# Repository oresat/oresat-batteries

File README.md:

# OreSat Battery Card

This is the battery card for the OreSat system. You can have up to four of these cards in any OreSat system, ID is set by resistors.

## Version History

- v1.0: We don't talk about v1 (EAGLE).
- v2.0: First true pack with 3D printed cell storage. Many small issues (EAGLE).
- v3.0: Flight ready pack, flown 2021-03-15 on OreSat0. Worked! (EAGLE).
- v3.1: Imported into KiCAD, small tweaks in process (KiCAD).

## Bill of Materials

- [PCBA](https://docs.google.com/spreadsheets/d/11vG1kWyrAjmbF5QJM-EhXmvQoF6O47japwYlHF802do/edit#gid=576852939)
- [Assembly](https://docs.google.com/spreadsheets/d/1GmZE2MR5q2XFSR2Y-65dwwPd7tem3i0CEjZBlCLeJBU/edit?usp=sharing)

## Mechanical CAD

- In [OnShape](https://cad.onshape.com/documents/5eda02ab87dc9021603c3619/w/adac4deb8bbe537007a3b153/e/e3b4fa777f54f6382aedf8d8).

## Technical Information

- 2 independent 2S1P 18650 battery packs (4 batteries total, in 2 packs). Each pack has:
   - Battery protection circuitry for charge and discharge control for each 2S1P pack
   - MAX17500 fuel gauge with cell balancing and cell temperature monitoring
- 3D printed battery holder, designed for CRP Windform SLS Nylon material (OK with Form3 Flame Retardant Resin).
- Positive battery lead disconnection switches (with room for plunger assemblies that go through OreSat +/-X rails).
- Satellite shutdown switches (!SHUTDOWN) (with room for plunger assemblies that go through OreSat +/-X rails).
- Flexible polyimide heater tapes to keep batteries above 0 C
- STM32F091 microcontroller (controlled by the OreSat Power Domain) to interface everything to the CAN bus

## TRANSITION DOCUMENT
Documentation is moving to [Google Docs](https://docs.google.com/document/d/1yaPGtJSM5RQG5k7sVpsDxBkVu4CHtm4LMNnisgOaNRg/edit#heading=h.gjdgxs). The rest of this readme will be integrated later.

## OreSat Vbus
OreSat main power bus is just our 2S Li Ion battery pack, which we've defined as 6.0 V minimum, 7.2 V typical, and 8.4 V maximum. Everything is directly connected to that bus, including:

- Other Oreat battery cards. For >= 2U CubeSats, you'll probably have at least two battery cards.
- All solar panels. Thus the solar panels see the direct battery voltage and can dump directly into the battery packs, thus doing _actual_ MPPT.
- All loads.

## Battery Card Topology
Confusingly, Each OreSat battery card has 2 independent battery packs on it. Each pack is made of a 2S1P 18650 LiPo cell pack. So it's a 2x2S1P if you will. Despite this, each card is independent and the OPD is fully capable of functioning with only one active card.

We decided to separate the packs instead of combining them into a single 2S2P pack for the sake of redundancy, we can lose one cell and the other pack can still provide power to the OPD, as opposed to losing an entire card from a single cell failure.  This design does come with the added drawbacks of extra overhead in the form of requiring more charge protection and fuel gauge circuitry.

## Charge/Discharge Protection
We are using Ablic S8209 to monitor our cell voltage levels and disable charging if the cell voltage goes above the predetermined overcharging threshold or disable discharging if the cell voltage goes below a predetermined discharging threshold.

The S8209 has two inputs that, if activated, will trigger the either the over-charge or under-charge protection to activate.  This allows us to daisy chain these chips together, so that each cell has its own charge protection IC.  It also allows us to connect them to a GPIO on an onboard microcontroller so that we can manually disable charging or discharging functionality if needed.  Below is a state diagram that depicts the desired behavior of our charging and discharging protection circuit

The output of the S8209 uses an internal N-channel MOSFET, which has the potential to latch from radiation exposure.   To combat this, we have P-channel MOSFETS in series with the VDD of each S8209, the gate of the MOSFET is connected to our onboard microcontroller, so that we can periodically power cycle the S8209 and clear the N-channel latch.

The actual control of charge and discharge are done using Linear LTC4412 ideal diode controllers. Totally bizarre, but indepdenently controllable!

## Fuel Gauge and Cell Health Monitoring
Each 2S1P battery back will have two MAX17205 fuel gauges to monitor the packs current state of charge, and the long term health of the battery.  Each MAX17205 will be reporting both the direct State of charge (in mAh) and the percentage over I2C to our M0, compensating for factors such as cell degradation and temperature ranges.  We are still testing the accuracy of the MAX17205's compensation algorithm's for extreme charge levels and temperature in our lab.  At this point we don't know how much we should be relying on these compensation algorithms, they could be amazing! Or horrible! We don't know! Yay science!

Each fuel gauge is also monitoring the battery temperatures with a single internal sensor and two external thermistors (we are still determining the best position for these thermistors).  This gives us a wackton of data which is good because we are data hoarders.

Finally the MAX17205 also does cell balancing, which we'll enable while charging.

## Heaters
Thermal models of both 1U and 2U CubeSats show an average "passive" battery temperature of ~ -10 C). That's not good. We can't charge the battery below 0 C. So we've added heaters to heat up the batteries when charging if necessary.

We're using two Minco HK6903 heaters in parallel. They have "vacuum OK" (apparently?) urethane PSA that we'll use to attach them to the batteries. Note that they're 12.7 x 100 mm, and each heater goes across both batteries. At 49 ohms +/- 10% each, that's 25 ohms in parallel. Unclear on the heater's tempco. We'll ignore for now.

- At 8.4V, that's 336 mA = 2.8 W (at 100% DC)
- At 6.0V, that's 240 mA = 1.4 W (at 100% DC)
- We can of course PWM them and reduce the power as necessary

With that much current draw, we're going to need to modify the OPD circuit breaker to allow more current.

## Batteries

- Tenergy model "30005-0 (ICR 18650-2600, LR1865SK)"
- Rated at 2600 mAh
- Max voltage: 4.2 V
- Typical voltage: 3.6 V
- Minimum voltage: 2.75 V
- Maximum charge current: 1.25 A
   - 0 - 45 C only
- Maximum discharge Current:
   - -20 - 5 C = 1.25 A
   -  5 - 45 C = 5 A
   - 45 - 60 C = 3.75 A

### Temperature

Just to summarize the battery temperature operational range:

- Cell temperature < -20 C -- DEAD
- Cell temperature < 0 C -- DISCHARGE ONLY
- Cell temperature < 45 C -- NORMAL OPERATION
- Cell temperature > 45 C-- DISCHARGE ONLY
- Cell temperature > 60 C-- DEAD

### Cell failure (short)

- Short will plummet battery to < 2.5V (Vlvco) and S-8209 will disconnect the battery from discharging but not charging

## Battery pack behaviors (circuitry + firmware)

- Automatic discharge if > 6.0 V
- Automatic slow charge if < 8.4 V
- Fast charge if battery pack within ~ 0.5 V of other batteries

## Hacking the OPD Circuit Breaker

The OPD circuit breaker is supposed to trip at 300 mA without any division at the current output. Since the headers could pull up to 336, we need to probably go up to that plus 50 mA. So we put in a 10K and 20K to make a 0.66 divider and an N CH MOSFET to turn on the divider on the signal "MOARPWR". Asserting MOARPWR should give you up to 400 mA.

## LICENSE

Copyright Portland State Aerospace Society 2020.

This documentation describes Open Hardware and is licensed under the CERN OHL v. 1.2.

You may redistribute and modify this documentation under the terms of the CERN OHL v.1.2. [http://ohwr.org/cernohl](http://ohwr.org/cernohl). This documentation is distributed WITHOUT ANY EXPRESS OR IMPLIED WARRANTY, INCLUDING OF MERCHANTABILITY, SATISFACTORY QUALITY AND FITNESS FOR A PARTICULAR PURPOSE. Please see the CERN OHL v.1.2 for applicable conditions.

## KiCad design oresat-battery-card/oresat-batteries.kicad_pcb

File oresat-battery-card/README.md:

---
title: "**OreSat Battery Card**"
subtitle: |
  **Fabrication and Assembly Information**\
  For build TIME-STAMP
fontsize: 10pt
geometry:
  - margin=0.5in
toc: true
toc-depth: 2
colorlinks: true
urlcolor: blue
---

\newpage

# About this Board

## Board Description

The OreSat Battery Card carries two packs of 2S1P 18650 Lithium Ion cells. It operates completely autonomously. The C3 card
can, however, turn on the Battery Card's OPD, which will enable the onboard microcontroller and the battery card will begin
sending telemetry over CAN, including from a fuel gauge for each battery pack.

The battery card has two heater strips, which firmware uses to heat the batteries to >= 5 C.

Their are four inhibit switches as well - two for the OreSat !SHUTDOWN circuit, one for positive battery disconnect, and 
one for negative battery disconnect.

## Documentation Links

- Git repository: <https://github.com/oresat/oresat-batteries>
- [Design Notes](https://docs.google.com/document/d/1yaPGtJSM5RQG5k7sVpsDxBkVu4CHtm4LMNnisgOaNRg/edit?usp=sharing)

## Documentation Files

| Filename                        | Notes                                    |
| ------------------------------- | ---------------------------------------- |
| README.pdf                      | This README file                         |
| PROJECT-NAME-outline.dxf        | Board outline (with holes) in DXF format |
| PROJECT-NAME-pcba.step          | 3D model of PCBA (with components)       |
| PROJECT-NAME-render-bot.jpg     | Render of the top of the 3D model        |
| PROJECT-NAME-render-bot.jpg     | Render of the bottom of the 3D model     |
| PROJECT-NAME-schematic.pdf      | PDF of board schematics                  |

## Contact Information

- Website: <https://www.oresat.org/>
- Email: <oresat@pdx.edu>
- Instagram: @pdxaerospace

## Board Renders

{width=50%}
{width=50%}

\newpage

# Printed Circuit Board (PCB) Fabrication Information

## Board Info

- 4 layer board
- Bounding box is 99.8 x 94.6 mm
- Board thickness is 1.59 mm

## Board Requirements

- Design Rules
    - Minimum Trace / Space design rules
       - Outer layers: 0.127 mm (5.0 mil) / 0.127 mm (5.0 mil)
       - Inner layers: 0.127 mm (5.0 mil) / 0.127 mm (5.0 mil)
    - Outer dimension router tolerance: +/- 0.254 mm (10.0 mil)
    - Hole placement tolerance: +/- 0.075 mm (3.0 mil)
    - Inner tab routed slot tolerance: +/- 0.254 mm (10.0 mil)
- Drills
   - Drill Positional Tolerance: 0.051 mm (2.0 mil)
   - Drill Size tolerance: +/- 0.064 mm (2.5 mil)
- Plated/Un-plated holes
  - Via/PTH minimum diameter: 0.254 mm (10 mil)
  - Via/PTH minimum annulus: 0.102 mm (4 mil) radius
- Outline/Routing
  - This board requires a 1 mm router bit.
- Slots
  - There are 16 slots.
- Cutouts
  - There are no cutouts
- There are 3 fiducials on the top layer.
- Panel tabs ("mouse bites")
   - Card edges must be smooth; no mouse bites or other intrusions into the card outline.
   - If external mouse bites are required, minimize and customer will remove by hand before assembly.
- If not otherwise specified, fabricate PCB to IPC 6012 Class 2 or better.

## Stackup /  Materials

- Outside copper layers is 1 oz Cu after plating (0.043 mm / 1.7 mil)
- Inside copper layers are 0.5 oz Cu (0.018 mm / 0.7 mil)
- There are no requirements on the prepreg or core of this four layer stackup.
- Board Surface treatment should be ENIG, althogh immersion Silver is acceptable.
- White silkscreen on top and bottom surface
- Taiyo PSR-4000 or equivalent soldermask on top and bottom, no requirements for color.

## Array / Panel Information

- Coordinate with Contract Manufacturer (CM) for optimal size of this panel.
- If no feedback from CM, then produce single boards (no panel).

## Fabrication Files

### IPC-2581 File

| Filename                 | Notes                                   |
| ------------------------ | --------------------------------------- |
| PROJECT-NAME-ipc2581.xml | IPC-2581 board information file         |

### Legacy PCB Files

| Filename                      | Notes                                         |
| ------------------------------| --------------------------------------------- |
| PROJECT-NAME-Edge_Cuts.gbr    | RS274X file for the dimension (outline) layer |
| PROJECT-NAME-F_Silkscreen.gbr | RS274X file for the top silkscreen            |
| PROJECT-NAME-F_Mask.gbr       | RS274X file for the top soldermask            |
| PROJECT-NAME-F_Cu.gbr         | RS274X file for the top copper layer          |
| PROJECT-NAME-In1_Cu.gbr       | RS274X file for the layer 2 copper            |
| PROJECT-NAME-In2_Cu.gbr       | RS274X file for the layer 3 copper            |
| PROJECT-NAME-B_Cu.gbr         | RS274X file for the bottom copper layer       |
| PROJECT-NAME-B_Mask.gbr       | RS274X file for the bottom soldermask         |
| PROJECT-NAME-B_Silkscreen.gbr | RS274X file for the bottom silkscreen         |
| PROJECT-NAME-NPTH.drl         | Excellon file for non-plated through holes    |
| PROJECT-NAME-PTH.drl          | Excellon file for plated through holes        | 

\newpage

# Printed Circuit Board Assembly (PCBA) Information

## Assembly Info

- All components are on the top side of the board.
- This PCBA uses both surface mount (SMT) and through-hole (THT) components.

## Assembly Requirements

- Assemble to IPC Class 2 or better
- Bake components that are not moisture sealed to appropriate levels as required.
- Any solder paste (leaded or RoHS) is acceptable. RoHS solder is slightly preferred.
- Any no-clean or aqueous wash flux is acceptable.
- No conformal coating.

## Component Specific Assembly Information

- ASSEMBLY OF THIS BATTERY CARD IS SAFETY CRITICAL. CAREFULLY FOLLOW THE ASSEMBLY SOP,
[PSAS SOP - OreSat Battery Card Assembly](https://docs.google.com/document/d/1YFvptCjQO5j7sZraa8bQpTQ43OzNet4JrRba6-A-SFA/edit?usp=sharing).

## Assembly Files

### IPC-2581 File

| Filename                 | Notes                           |
| ------------------------ | ------------------------------- |
| PROJECT-NAME-ipc2581.xml | IPC-2581 board information file |

### Bill of Materials (BOM)

| Filename             | Description                            |
| -------------------- | -------------------------------------- |
| PROJECT-NAME-bom.csv | BOM in Comma Separated Variable format |

### Solder Paste Stencils

| Filename                 | Notes                                            |
| ------------------------ | ------------------------------------------------ |
| PROJECT-NAME-B_Paste.gbr | RS274X file for top/front solder paste stencil   |
| PROJECT-NAME-F_Paste.gbr | RS274X file for bottom/back solder paste stencil |

### Mounting/Placement Location

| Filename            | Description                                 |
| ------------------- | ------------------------------------------- |
| PROJECT-NAME.pos | Pick and place locations for components     |

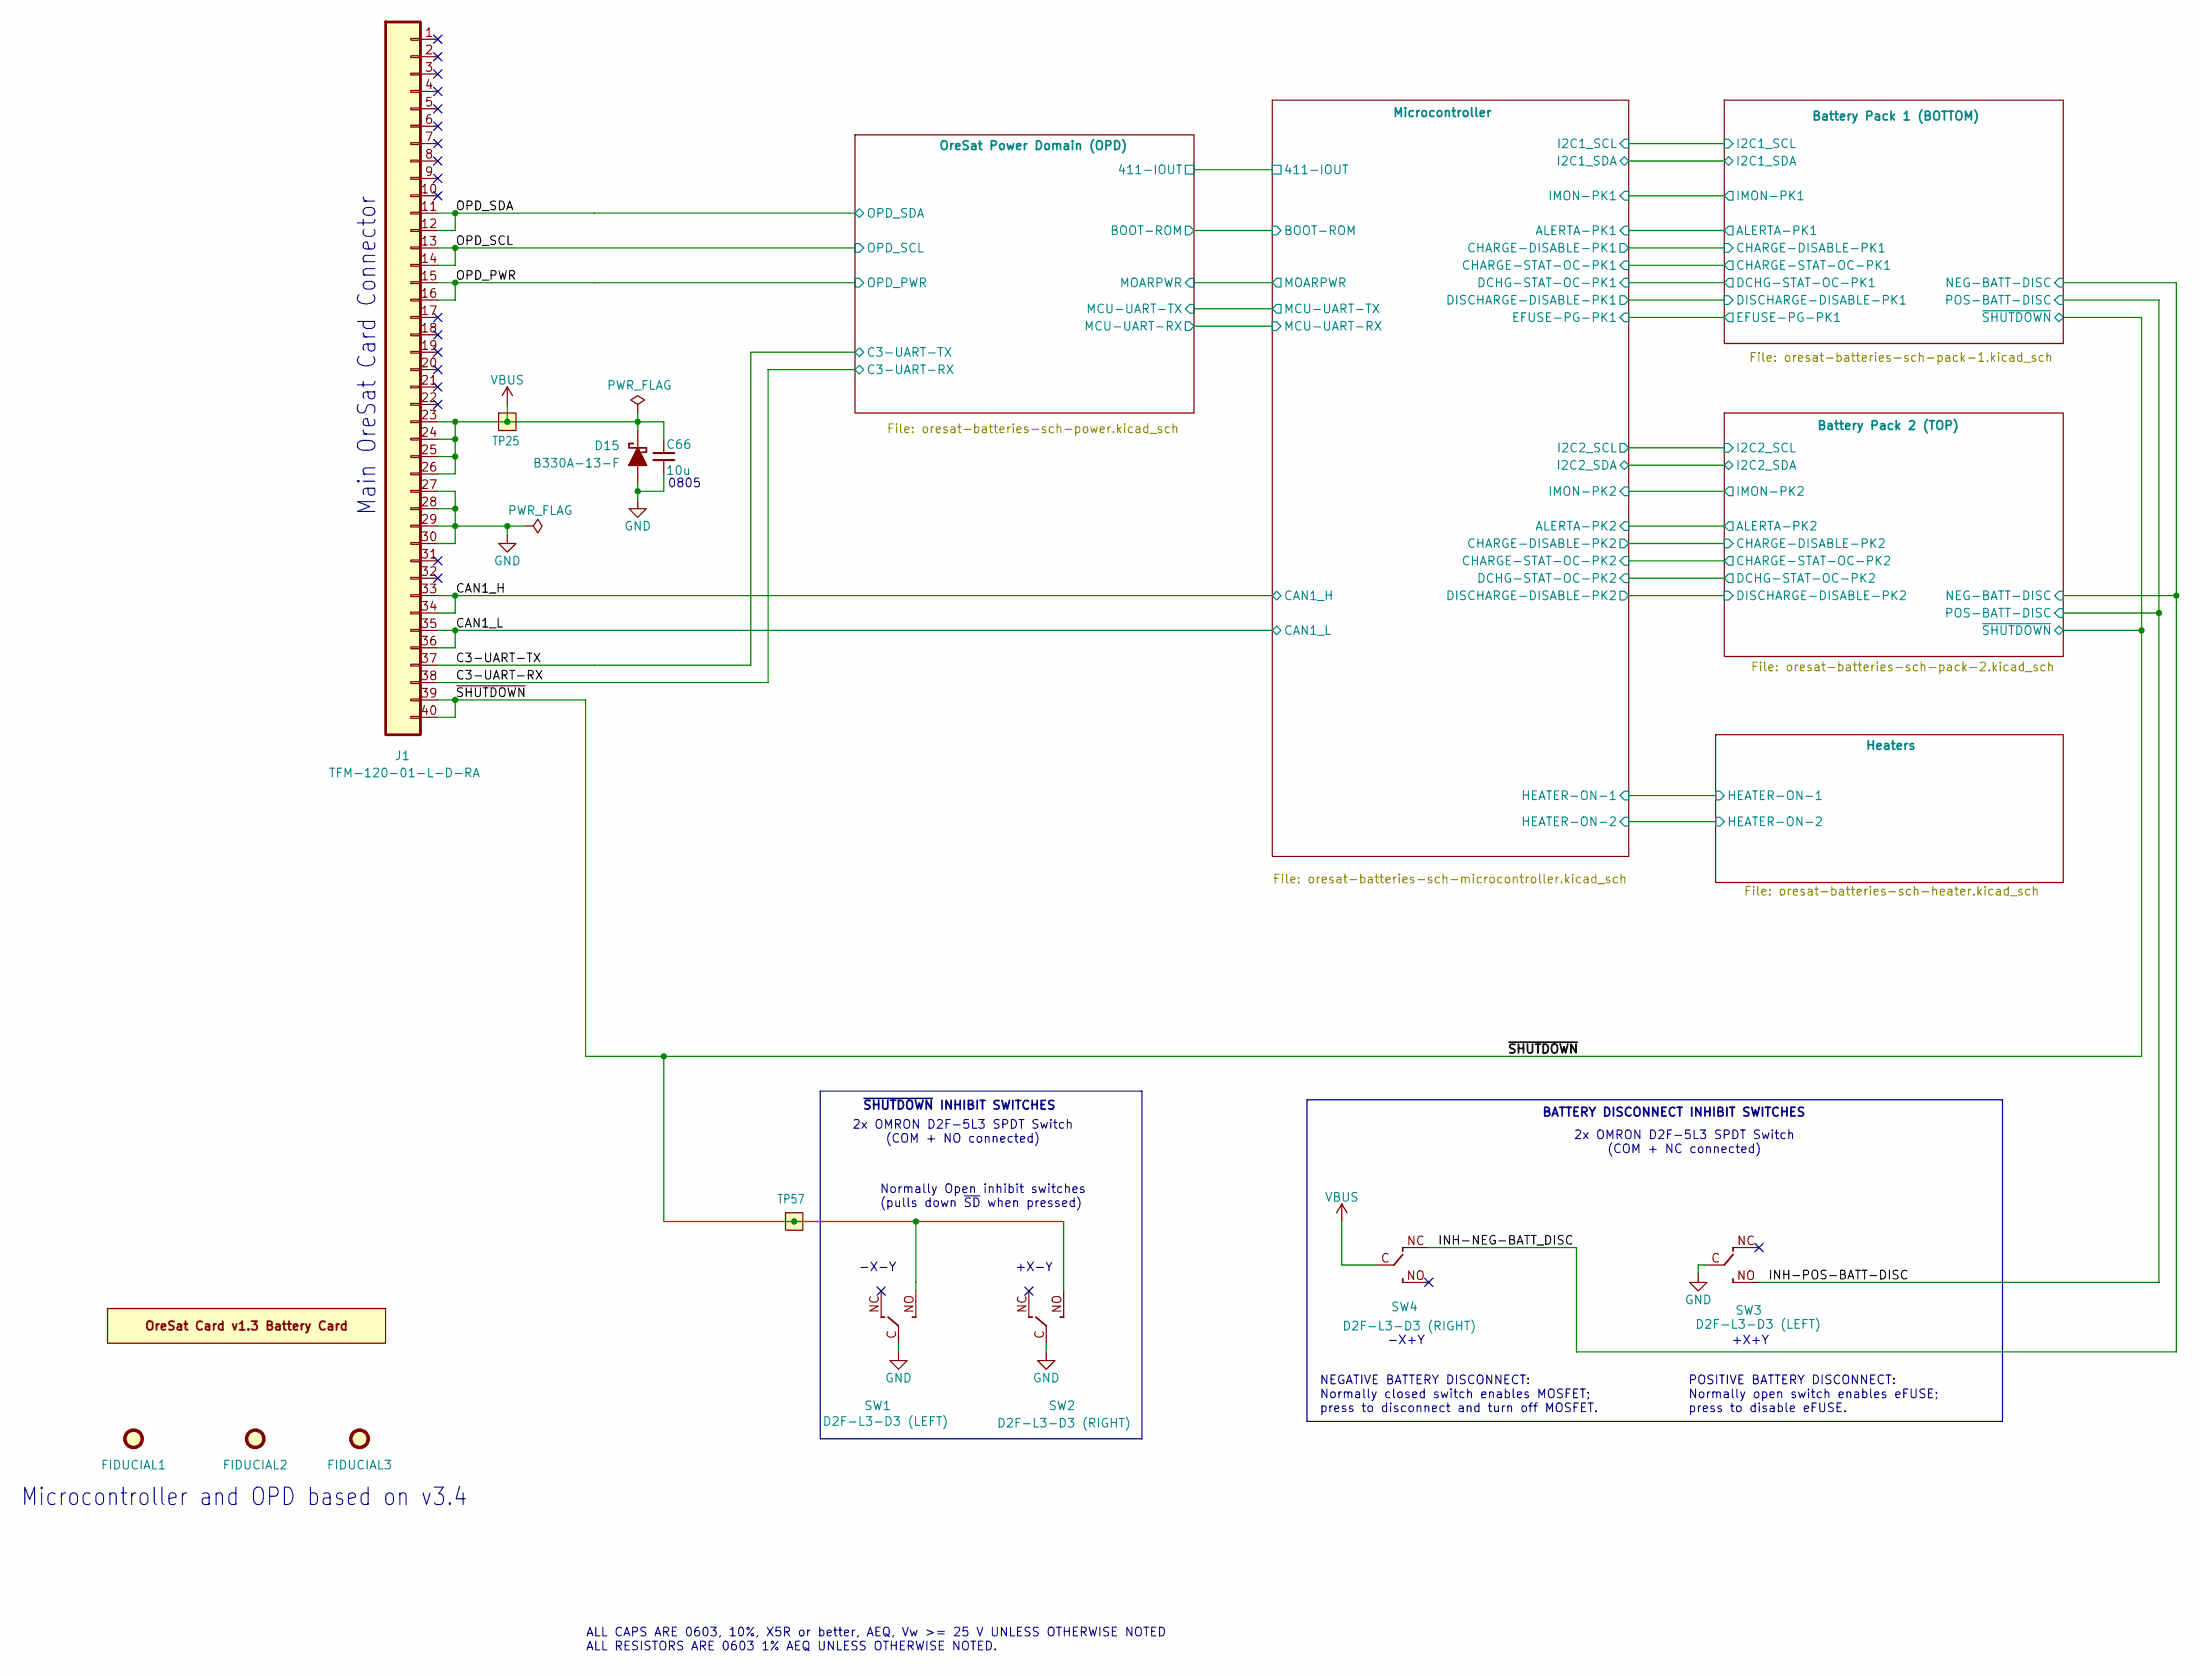
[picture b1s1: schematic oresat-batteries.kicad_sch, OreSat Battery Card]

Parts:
C66: 10u; 0805-C-NOSILK; MPN GRT21BC71E106KE13K
D15: B330A-13-F; D_SMA; MPN B330A-13-F
FIDUCIAL1, FIDUCIAL2, FIDUCIAL3: FIDUCIAL-1.0X2.0; Fiducial_1mm_Mask2mm
J1: TFM-120-01-L-D-RA; J-SAMTEC-TFM-120-X1-XXX-D-RA; MPN TFM-120-01-L-D-RA
PCB1: ORESAT-CARD-V1.3-BATTERY; ORESAT-CARD-V1.3-BATTERY-V3.0; MPN N/A
SW1, SW3: D2F-L3-D3 (LEFT); D2F-L3-D3-HORIZONTAL-L; MPN D2F-L3-D3
SW2, SW4: D2F-L3-D3 (RIGHT); D2F-L3-D3-HORIZONTAL-R; MPN D2F-L3-D3
TP25, TP57: TEST-POINT-LARGE-SQUARE; TestPoint-0.75mm-th

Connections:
/C3-UART-RX: J1.38; also elsewhere on the board
/C3-UART-TX: J1.37; also elsewhere on the board
/CAN1_H: J1.33, J1.34; also elsewhere on the board
/CAN1_L: J1.35, J1.36; also elsewhere on the board
/INH-NEG-BATT_DISC: SW4.NC; also elsewhere on the board
/INH-POS-BATT-DISC: SW3.NO; also elsewhere on the board
/OPD_PWR: J1.15, J1.16; also elsewhere on the board
/OPD_SCL: J1.13, J1.14; also elsewhere on the board
/OPD_SDA: J1.11, J1.12; also elsewhere on the board
/~SHUTDOWN: J1.39, J1.40, SW1.NO, SW2.NO, TP57.1 (1_1); also elsewhere on the board
GND: C66.2, D15.2 (A), J1.27, J1.28, J1.29, J1.30, SW1.C (COM), SW2.C (COM), SW3.C (COM); also elsewhere on the board
VBUS: C66.1, D15.1 (K), J1.23, J1.24, J1.25, J1.26, SW4.C (COM), TP25.1 (1_1); also elsewhere on the board

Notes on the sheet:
Normally Open inhibit switches (pulls down ~{SD} when pressed)
Main OreSat Card Connector
~{SHUTDOWN} INHIBIT SWITCHES
BATTERY DISCONNECT INHIBIT SWITCHES
+X+Y
2x OMRON D2F-5L3 SPDT Switch (COM + NO connected)
-X-Y
ALL CAPS ARE 0603, 10%, X5R or better, AEQ, Vw >= 25 V UNLESS OTHERWISE NOTED ALL RESISTORS ARE 0603 1% AEQ UNLESS OTHERWISE NOTED.
+X-Y
-X+Y
0805
Microcontroller and OPD based on v3.4
NEGATIVE BATTERY DISCONNECT: Normally closed switch enables MOSFET; press to disconnect and turn off MOSFET.
2x OMRON D2F-5L3 SPDT Switch (COM + NC connected)
POSITIVE BATTERY DISCONNECT: Normally open switch enables eFUSE; press to disable eFUSE.

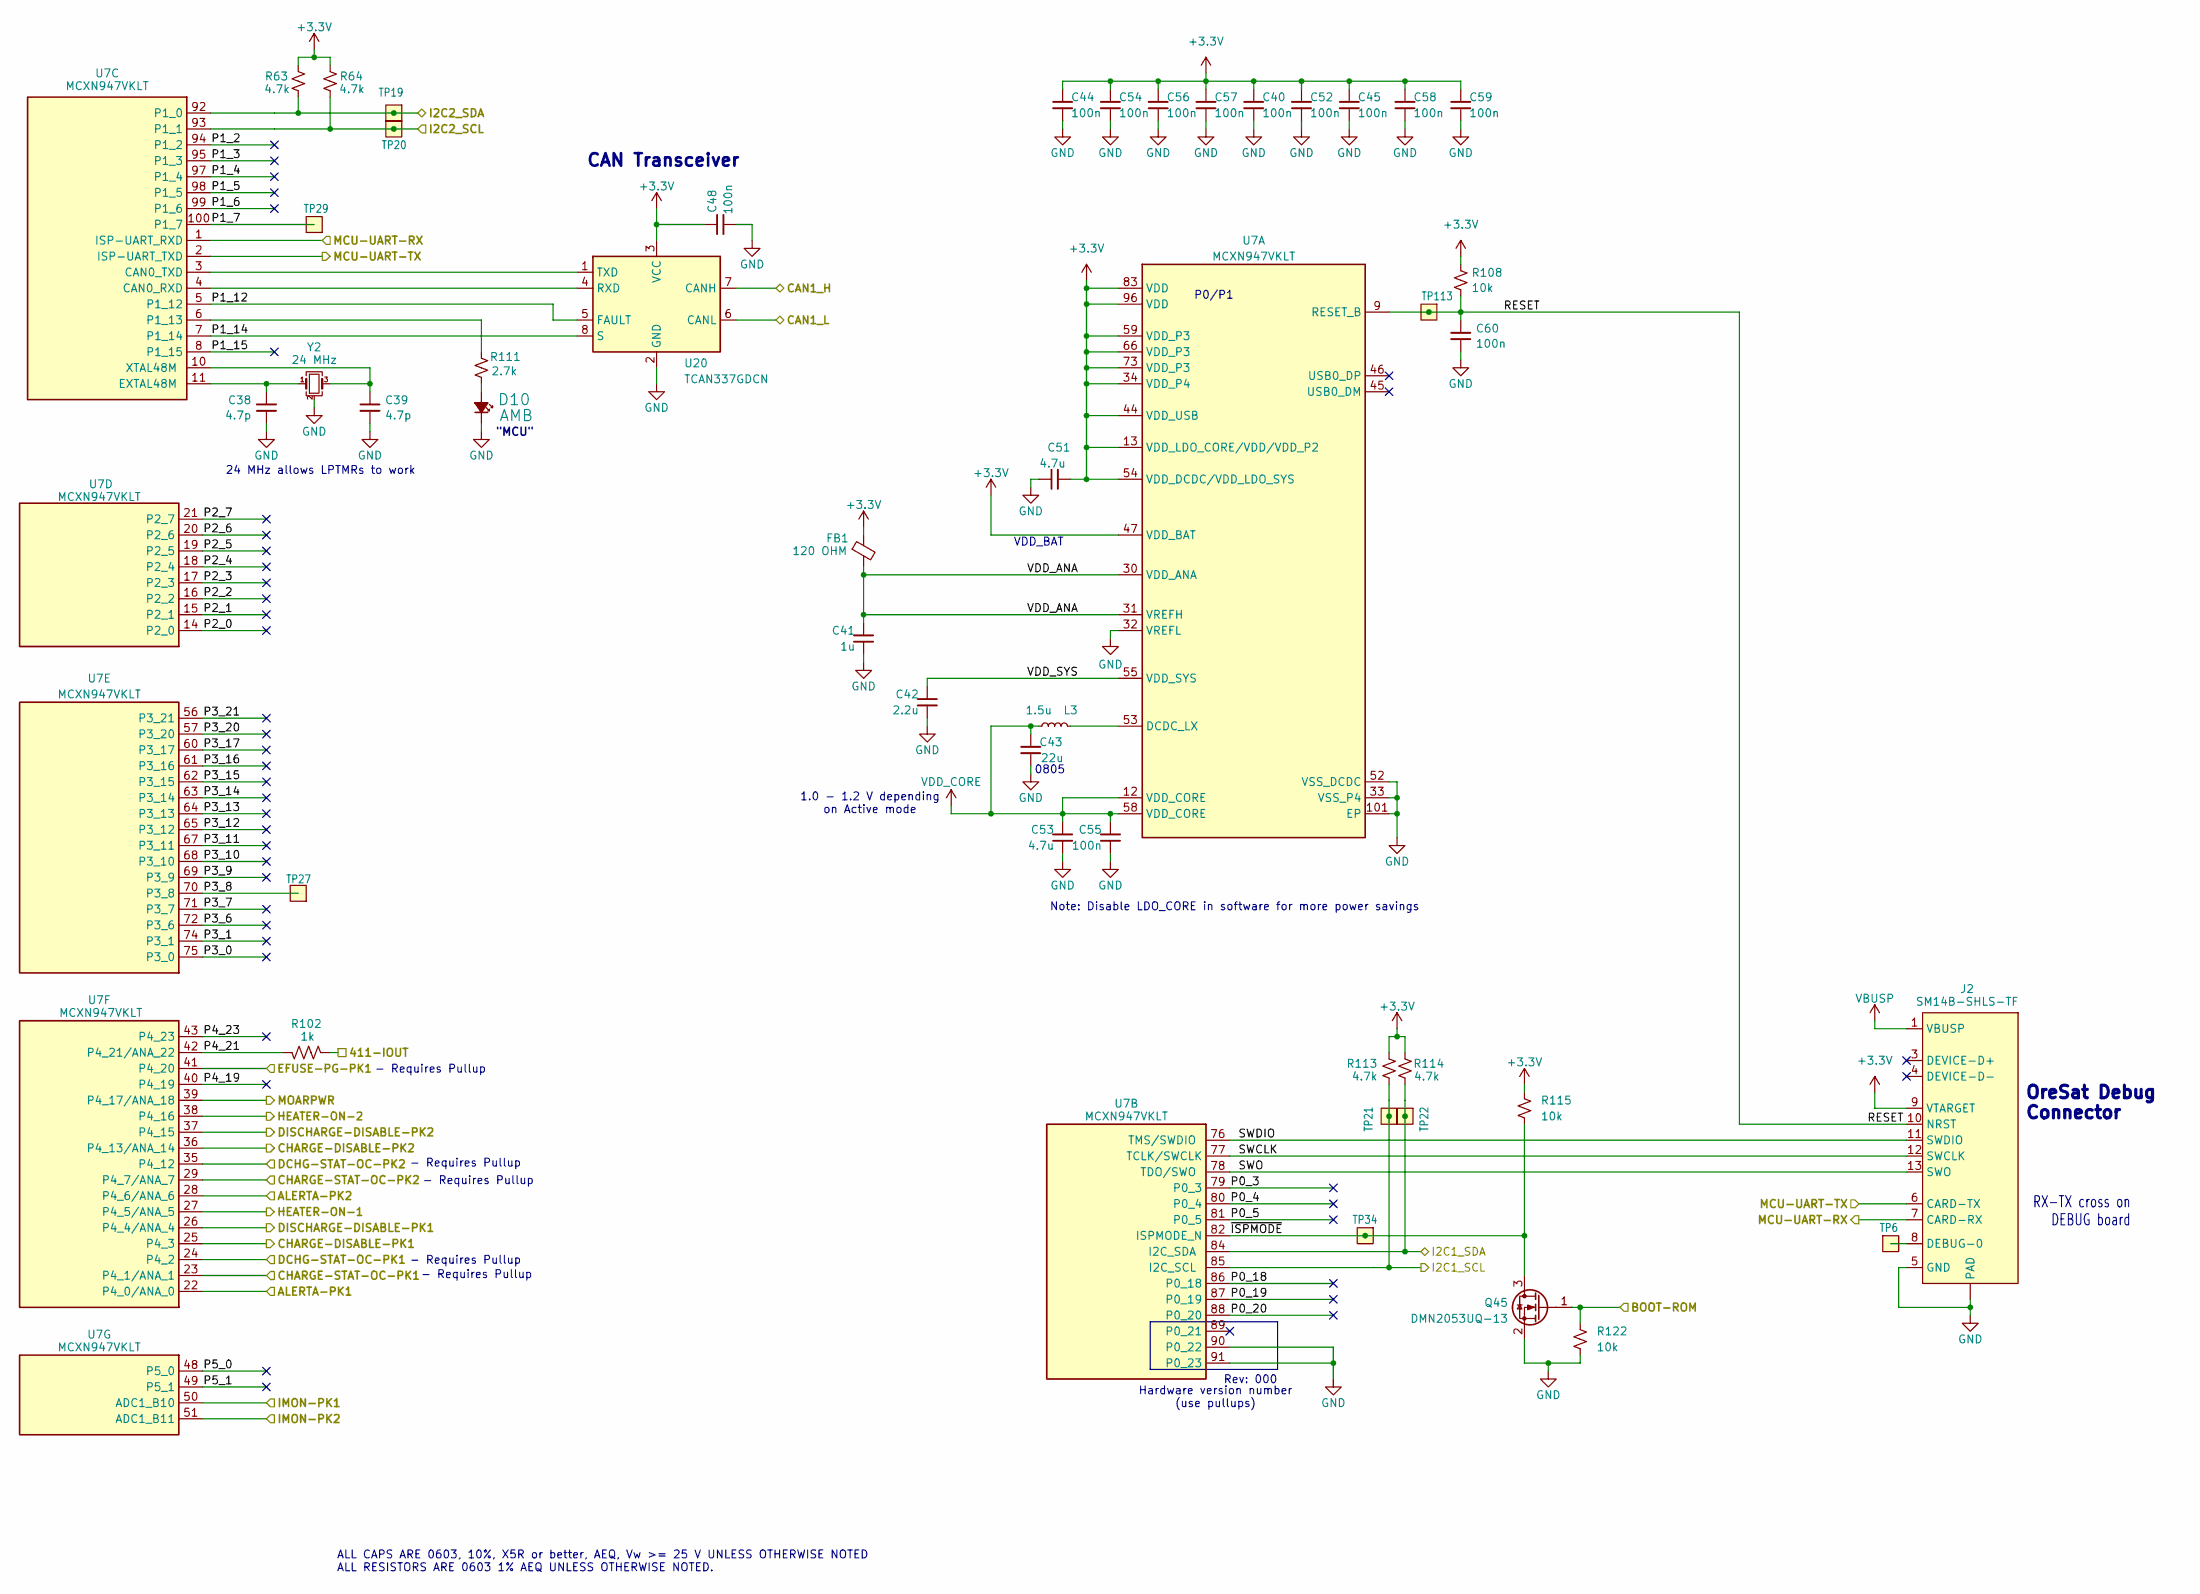
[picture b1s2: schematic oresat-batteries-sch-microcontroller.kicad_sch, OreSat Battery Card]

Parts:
C38, C39: 4.7p; 0603-C-NOSILK; MPN C0603C479D5GACAUTO
C40, C44, C45, C48, C52, C54, C55, C56, C57, C58, C59, C60: 100n; 0603-C-NOSILK; MPN C0603C104K5RACAUTO
C41: 1u; 0603-C-NOSILK; MPN GRT188R71E105KE13D
C42: 2.2u; 0603-C-NOSILK; MPN GRT188C71E225KE13D
C43: 22u; 0805-C-NOSILK; MPN GRT21BC81C226ME13L
C51, C53: 4.7u; 0805-C-NOSILK; MPN GRT21BC71E475KE13L
D10: AMB; LED_0603_1608Metric; MPN 150060AS75000
FB1: 120 OHM; 0805-B-NOSILK; MPN 2508051217Y6
J2: SM14B-SHLS-TF; J-JST-SM14BSHLSTF; MPN SM14B-SHLS-TF
L3: 1.5u; L_0805_2012Metric; MPN SRP2012TMA-1R5M
Q45: DMN2053UQ-13; SOT-23; MPN DMN2053UQ-13
R63, R64, R113, R114: 4.7k; 0603-C-NOSILK; MPN RMCF0603FT4K70
R102: 1k; 0603-C-NOSILK; MPN RMCF0603FT1K00
R108, R115, R122: 10k; 0603-C-NOSILK; MPN RMCF0603FT10K0
R111: 2.7k; 0603-C-NOSILK; MPN RMCF0603FT2K70
TP6, TP113: Test-Point; TestPoint-0.75mm-th
TP19, TP20, TP21, TP22, TP27, TP29, TP34: TEST-POINT-LARGE-SQUARE; TestPoint-0.75mm-th
U7: MCXN947VKLT; MCXN947KVLT-QFP50P1600X1600X160-101N; MPN MCXN947VKLT
U20: TCAN337GDCN; SOT-23-8; MPN TCAN337GDCNT
Y2: 24 MHz; Crystal_SMD_2016-4Pin_2.0x1.6mm; MPN 830108212309

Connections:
+3.3V: C40.1, C44.1, C45.1, C48.2, C51.1, C52.1, C54.1, C56.1, C57.1, C58.1, C59.1, FB1.1, J2.9 (VTARGET), R63.2, R64.2, R108.2, R113.2, R114.2, R115.2, U7.13 (VDD_LDO_CORE/VDD/VDD_P2), U7.34 (VDD_P4), U7.44 (VDD_USB), U7.47 (VDD_BAT), U7.54 (VDD_DCDC/VDD_LDO_SYS), U7.59 (VDD_P3), U7.66 (VDD_P3), U7.73 (VDD_P3), U7.83 (VDD), U7.96 (VDD), U20.3 (VCC); also elsewhere on the board
/Battery Pack 1 (BOTTOM)/ALERTA-PK1: U7.22 (P4_0/ANA_0); also elsewhere on the board
/Battery Pack 1 (BOTTOM)/CHARGE-DISABLE-PK1: U7.25 (P4_3); also elsewhere on the board
/Battery Pack 1 (BOTTOM)/CHARGE-STAT-OC-PK1: U7.23 (P4_1/ANA_1); also elsewhere on the board
/Battery Pack 1 (BOTTOM)/DCHG-STAT-OC-PK1: U7.24 (P4_2); also elsewhere on the board
/Battery Pack 1 (BOTTOM)/DISCHARGE-DISABLE-PK1: U7.26 (P4_4/ANA_4); also elsewhere on the board
/Battery Pack 1 (BOTTOM)/EFUSE-PG-PK1: U7.41 (P4_20); also elsewhere on the board
/Battery Pack 1 (BOTTOM)/I2C1_SCL: R113.1, TP21.1 (1_1), U7.85 (I2C_SCL); also elsewhere on the board
/Battery Pack 1 (BOTTOM)/I2C1_SDA: R114.1, TP22.1 (1_1), U7.84 (I2C_SDA); also elsewhere on the board
/Battery Pack 1 (BOTTOM)/IMON-PK1: U7.50 (ADC1_B10); also elsewhere on the board
/Battery Pack 2 (TOP)/ALERTA-PK2: U7.28 (P4_6/ANA_6); also elsewhere on the board
/Battery Pack 2 (TOP)/CHARGE-DISABLE-PK2: U7.36 (P4_13/ANA_14); also elsewhere on the board
/Battery Pack 2 (TOP)/CHARGE-STAT-OC-PK2: U7.29 (P4_7/ANA_7); also elsewhere on the board
/Battery Pack 2 (TOP)/DCHG-STAT-OC-PK2: U7.35 (P4_12); also elsewhere on the board
/Battery Pack 2 (TOP)/DISCHARGE-DISABLE-PK2: U7.37 (P4_15); also elsewhere on the board
/Battery Pack 2 (TOP)/I2C2_SCL: R64.1, TP20.1 (1_1), U7.93 (P1_1); also elsewhere on the board
/Battery Pack 2 (TOP)/I2C2_SDA: R63.1, TP19.1 (1_1), U7.92 (P1_0); also elsewhere on the board
/Battery Pack 2 (TOP)/IMON-PK2: U7.51 (ADC1_B11); also elsewhere on the board
/CAN1_H: U20.7 (CANH); also elsewhere on the board
/CAN1_L: U20.6 (CANL); also elsewhere on the board
/Heaters/HEATER-ON-1: U7.27 (P4_5/ANA_5); also elsewhere on the board
/Heaters/HEATER-ON-2: U7.38 (P4_16); also elsewhere on the board
/Microcontroller/411-IOUT: R102.2; also elsewhere on the board
/Microcontroller/BOOT-ROM: Q45.1 (G), R122.2; also elsewhere on the board
/Microcontroller/MCU-UART-RX: J2.7 (CARD-RX), U7.1 (ISP-UART_RXD); also elsewhere on the board
/Microcontroller/MCU-UART-TX: J2.6 (CARD-TX), U7.2 (ISP-UART_TXD); also elsewhere on the board
/Microcontroller/MOARPWR: U7.39 (P4_17/ANA_18); also elsewhere on the board
/Microcontroller/P0_3: U7.79 (P0_3)
/Microcontroller/P0_4: U7.80 (P0_4)
/Microcontroller/P0_5: U7.81 (P0_5)
/Microcontroller/P0_18: U7.86 (P0_18)
/Microcontroller/P0_19: U7.87 (P0_19)
/Microcontroller/P0_20: U7.88 (P0_20)
/Microcontroller/P1_2: U7.94 (P1_2)
/Microcontroller/P1_3: U7.95 (P1_3)
/Microcontroller/P1_4: U7.97 (P1_4)
/Microcontroller/P1_5: U7.98 (P1_5)
/Microcontroller/P1_6: U7.99 (P1_6)
/Microcontroller/P1_7: TP29.1 (1_1), U7.100 (P1_7)
/Microcontroller/P1_12: U7.5 (P1_12), U20.5 (FAULT)
/Microcontroller/P1_14: U7.7 (P1_14), U20.8 (S)
/Microcontroller/P1_15: U7.8 (P1_15)
/Microcontroller/P2_0: U7.14 (P2_0)
/Microcontroller/P2_1: U7.15 (P2_1)
/Microcontroller/P2_2: U7.16 (P2_2)
/Microcontroller/P2_3: U7.17 (P2_3)
/Microcontroller/P2_4: U7.18 (P2_4)
/Microcontroller/P2_5: U7.19 (P2_5)
/Microcontroller/P2_6: U7.20 (P2_6)
/Microcontroller/P2_7: U7.21 (P2_7)
/Microcontroller/P3_0: U7.75 (P3_0)
/Microcontroller/P3_1: U7.74 (P3_1)
/Microcontroller/P3_6: U7.72 (P3_6)
/Microcontroller/P3_7: U7.71 (P3_7)
/Microcontroller/P3_8: TP27.1 (1_1), U7.70 (P3_8)
/Microcontroller/P3_9: U7.69 (P3_9)
/Microcontroller/P3_10: U7.68 (P3_10)
/Microcontroller/P3_11: U7.67 (P3_11)
/Microcontroller/P3_12: U7.65 (P3_12)
/Microcontroller/P3_13: U7.64 (P3_13)
/Microcontroller/P3_14: U7.63 (P3_14)
/Microcontroller/P3_15: U7.62 (P3_15)
/Microcontroller/P3_16: U7.61 (P3_16)
/Microcontroller/P3_17: U7.60 (P3_17)
/Microcontroller/P3_20: U7.57 (P3_20)
/Microcontroller/P3_21: U7.56 (P3_21)
/Microcontroller/P4_19: U7.40 (P4_19)
/Microcontroller/P4_21: R102.1, U7.42 (P4_21/ANA_22)
/Microcontroller/P4_23: U7.43 (P4_23)
/Microcontroller/P5_0: U7.48 (P5_0)
/Microcontroller/P5_1: U7.49 (P5_1)
/Microcontroller/RESET: C60.1, J2.10 (NRST), R108.1, TP113.1 (1_1), U7.9 (RESET_B)
/Microcontroller/SWCLK: J2.12 (SWCLK), U7.77 (TCLK/SWCLK)
/Microcontroller/SWDIO: J2.11 (SWDIO), U7.76 (TMS/SWDIO)
/Microcontroller/SWO: J2.13 (SWO), U7.78 (TDO/SWO)
/Microcontroller/VDD_ANA: C41.1, FB1.2, U7.30 (VDD_ANA), U7.31 (VREFH)
/Microcontroller/VDD_SYS: C42.1, U7.55 (VDD_SYS)
/Microcontroller/~ISPMODE: Q45.3 (D), R115.1, TP34.1 (1_1), U7.82 (ISPMODE_N)
GND: C38.2, C39.2, C40.2, C41.2, C42.2, C43.2, C44.2, C45.2, C48.1, C51.2, C52.2, C53.2, C54.2, C55.2, C56.2, C57.2, C58.2, C59.2, C60.2, D10.1 (K), J2.5 (GND), J2.14 (GND), J2.15 (PAD), J2.16 (PAD), Q45.2 (S), R122.1, U7.32 (VREFL), U7.33 (VSS_P4), U7.52 (VSS_DCDC), U7.90 (P0_22), U7.91 (P0_23), U7.101 (EP), U20.2 (GND), Y2.2 (G), Y2.4 (G); also elsewhere on the board
unnamed: D10.2 (A), R111.1
unnamed: J2.8 (DEBUG-0), TP6.1 (1_1)
unnamed: L3.2, U7.53 (DCDC_LX)
unnamed: R111.2, U7.6 (P1_13)
unnamed: C39.1, U7.10 (XTAL48M), Y2.3
unnamed: C38.1, U7.11 (EXTAL48M), Y2.1
unnamed: U7.4 (CAN0_RXD), U20.4 (RXD)
unnamed: U7.3 (CAN0_TXD), U20.1 (TXD)
VBUSP: J2.1 (VBUSP), J2.2 (VBUSP); also elsewhere on the board
VDD_CORE: C43.1, C53.1, C55.1, L3.1, U7.12 (VDD_CORE), U7.58 (VDD_CORE)

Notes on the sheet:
"MCU"
Note: Disable LDO_CORE in software for more power savings
- Requires Pullup
CAN Transceiver
ALL CAPS ARE 0603, 10%, X5R or better, AEQ, Vw >= 25 V UNLESS OTHERWISE NOTED ALL RESISTORS ARE 0603 1% AEQ UNLESS OTHERWISE NOTED.
Rev: 000
OreSat Debug Connector
1.0 - 1.2 V depending on Active mode
VDD_BAT
Hardware version number (use pullups)
P0/P1
24 MHz allows LPTMRs to work
0805
RX-TX cross on DEBUG board

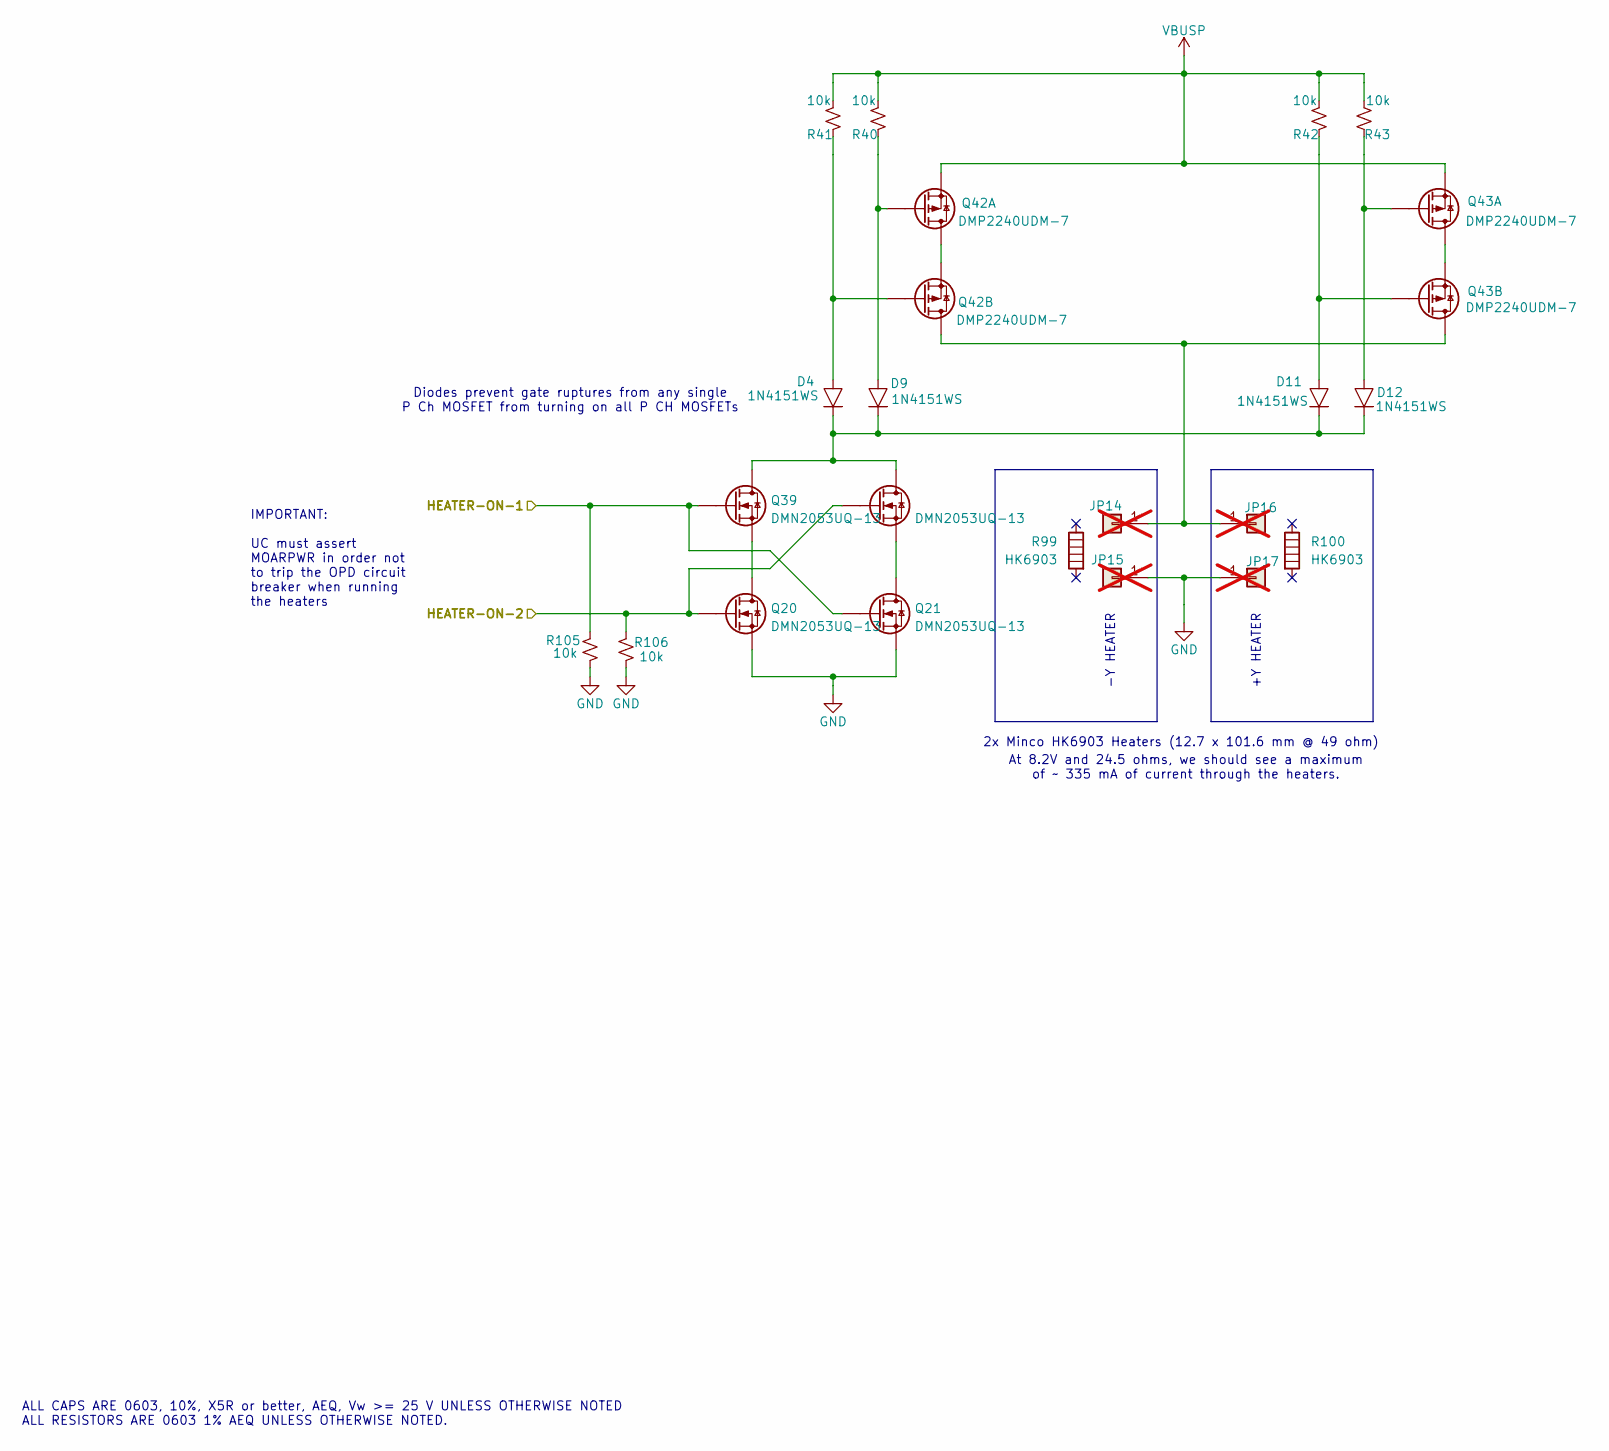
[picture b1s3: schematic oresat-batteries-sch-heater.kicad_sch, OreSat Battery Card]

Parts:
D4, D9, D11, D12: 1N4151WS; D_SOD-323; MPN 1N4151WS-E3-08
JP14, JP15, JP16, JP17: PINHD-1X1; PinHeader_1x01_P2.54mm_Vertical; MPN N/A; not fitted
Q20, Q21, Q38, Q39: DMN2053UQ-13; SOT-23; MPN DMN2053UQ-13
Q42, Q43: DMP2240UDM-7; SOT-23-6; MPN DMP2240UDM-7
R40, R41, R42, R43, R105, R106: 10k; 0603-C-NOSILK; MPN RMCF0603FT10K0
R99, R100: HK6903; MPN HK6903

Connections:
/Heaters/HEATER-ON-1: Q21.1 (G), Q39.1 (G), R105.2; also elsewhere on the board
/Heaters/HEATER-ON-2: Q20.1 (G), Q38.1 (G), R106.2; also elsewhere on the board
GND: JP15.1 (Pin_1_1), JP17.1 (Pin_1_1), Q20.2 (S), Q21.2 (S), R105.1, R106.1; also elsewhere on the board
unnamed: JP14.1 (Pin_1_1), JP16.1 (Pin_1_1), Q42.4 (D), Q43.4 (D)
unnamed: Q20.3 (D), Q39.2 (S)
unnamed: Q21.3 (D), Q38.2 (S)
unnamed: D4.1, D9.1, D11.1, D12.1, Q38.3 (D), Q39.3 (D)
unnamed: Q42.2 (S), Q42.6 (D)
unnamed: D9.2, Q42.1 (G), R40.1
unnamed: D4.2, Q42.3 (G), R41.1
unnamed: Q43.2 (S), Q43.6 (D)
unnamed: D12.2, Q43.1 (G), R43.1
unnamed: D11.2, Q43.3 (G), R42.1
VBUSP: Q42.5 (S), Q43.5 (S), R40.2, R41.2, R42.2, R43.2; also elsewhere on the board

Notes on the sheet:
IMPORTANT: UC must assert MOARPWR in order not to trip the OPD circuit breaker when running the heaters
2x Minco HK6903 Heaters (12.7 x 101.6 mm @ 49 ohm)
At 8.2V and 24.5 ohms, we should see a maximum of ~ 335 mA of current through the heaters.
+Y HEATER
Diodes prevent gate ruptures from any single P Ch MOSFET from turning on all P CH MOSFETs
-Y HEATER
ALL CAPS ARE 0603, 10%, X5R or better, AEQ, Vw >= 25 V UNLESS OTHERWISE NOTED ALL RESISTORS ARE 0603 1% AEQ UNLESS OTHERWISE NOTED.
